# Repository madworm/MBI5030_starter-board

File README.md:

MBI5030_starter-board
=====================

LAYOUT FILES: Simple breadboard starter board for the MBI5030. Includes 16 SMD LEDs for instant light. 

You will find code for this project in [this](https://github.com/madworm/MBI5030_demo) repository.

---

Before having PC-boards made, please make sure you know about your manufacturer's peculiarities!
Especially drill-sizes and their tolerances may vary too much and give you trouble.

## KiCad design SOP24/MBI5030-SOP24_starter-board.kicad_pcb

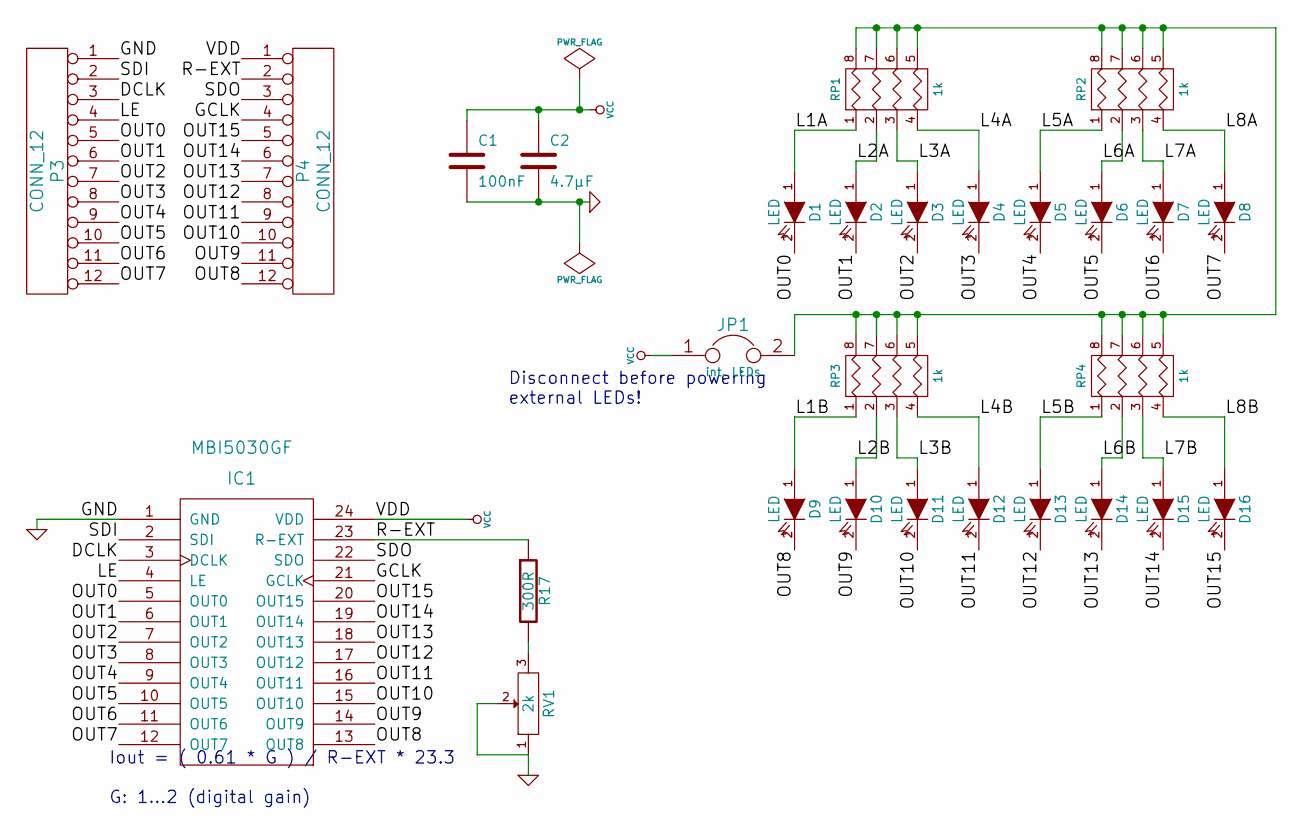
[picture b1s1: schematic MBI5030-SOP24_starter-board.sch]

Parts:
C1: 100nF
C2: 4.7µF
D1, D2, D3, D4, D5, D6, D7, D8, D9, D10, D11, D12, D13, D14, D15, D16: LED
IC1: MBI5030GF
JP1: int. LEDs
P3, P4: CONN_12
R17: 300R
RP1, RP2, RP3, RP4: 1k
RV1: 2k

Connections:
/DCLK: IC1.3 (DCLK), P3.3
/GCLK: IC1.21 (GCLK), P4.4
/L1A: D1.1 (A), RP1.1
/L1B: D9.1 (A), RP3.1
/L2A: D2.1 (A), RP1.2
/L2B: D10.1 (A), RP3.2
/L3A: D3.1 (A), RP1.3
/L3B: D11.1 (A), RP3.3
/L4A: D4.1 (A), RP1.4
/L4B: D12.1 (A), RP3.4
/L5A: D5.1 (A), RP2.1
/L5B: D13.1 (A), RP4.1
/L6A: D6.1 (A), RP2.2
/L6B: D14.1 (A), RP4.2
/L7A: D7.1 (A), RP2.3
/L7B: D15.1 (A), RP4.3
/L8A: D8.1 (A), RP2.4
/L8B: D16.1 (A), RP4.4
/LE: IC1.4 (LE), P3.4
/OUT0: D1.2 (K), IC1.5 (OUT0), P3.5
/OUT1: D2.2 (K), IC1.6 (OUT1), P3.6
/OUT2: D3.2 (K), IC1.7 (OUT2), P3.7
/OUT3: D4.2 (K), IC1.8 (OUT3), P3.8
/OUT4: D5.2 (K), IC1.9 (OUT4), P3.9
/OUT5: D6.2 (K), IC1.10 (OUT5), P3.10
/OUT6: D7.2 (K), IC1.11 (OUT6), P3.11
/OUT7: D8.2 (K), IC1.12 (OUT7), P3.12
/OUT8: D9.2 (K), IC1.13 (OUT8), P4.12
/OUT9: D10.2 (K), IC1.14 (OUT9), P4.11
/OUT10: D11.2 (K), IC1.15 (OUT10), P4.10
/OUT11: D12.2 (K), IC1.16 (OUT11), P4.9
/OUT12: D13.2 (K), IC1.17 (OUT12), P4.8
/OUT13: D14.2 (K), IC1.18 (OUT13), P4.7
/OUT14: D15.2 (K), IC1.19 (OUT14), P4.6
/OUT15: D16.2 (K), IC1.20 (OUT15), P4.5
/R-EXT: IC1.23 (R-EXT), P4.2, R17.1
/SDI: IC1.2 (SDI), P3.2
/SDO: IC1.22 (SDO), P4.3
GND: C1.2, C2.2, IC1.1 (GND), P3.1, RV1.1, RV1.2
unnamed: R17.2, RV1.3
unnamed: JP1.2, RP1.5 (R4), RP1.6 (R3), RP1.7 (R2), RP1.8 (R1), RP2.5 (R4), RP2.6 (R3), RP2.7 (R2), RP2.8 (R1), RP3.5 (R4), RP3.6 (R3), RP3.7 (R2), RP3.8 (R1), RP4.5 (R4), RP4.6 (R3), RP4.7 (R2), RP4.8 (R1)
VCC: C1.1, C2.1, IC1.24 (VDD), JP1.1, P4.1

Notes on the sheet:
Iout = ( 0.61 * G ) / R-EXT * 23.3 G: 1...2 (digital gain)
Disconnect before powering external LEDs!

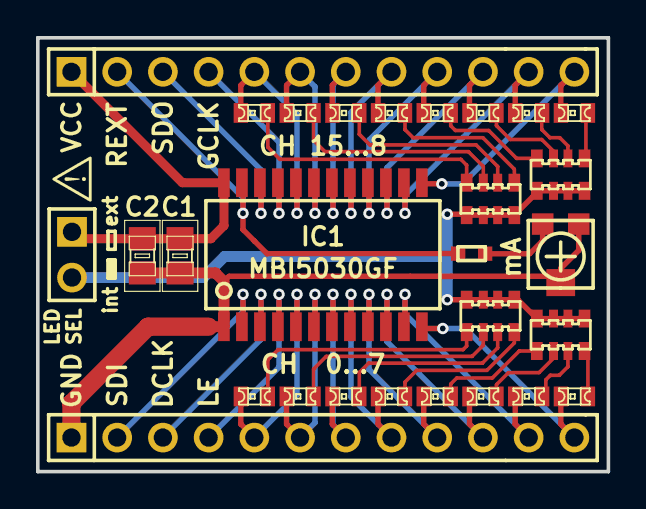
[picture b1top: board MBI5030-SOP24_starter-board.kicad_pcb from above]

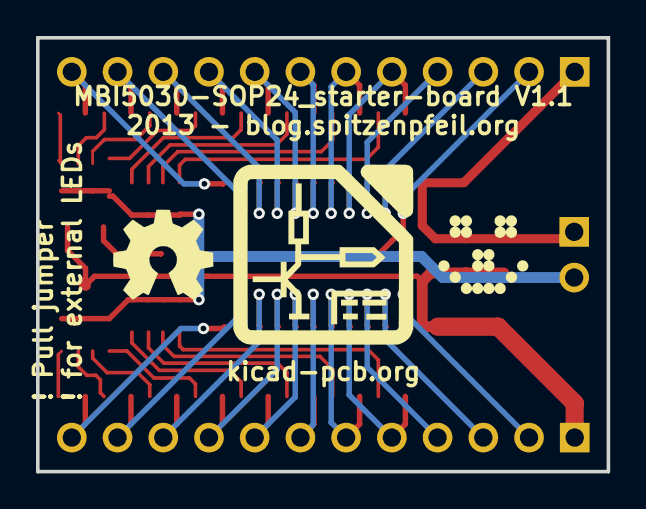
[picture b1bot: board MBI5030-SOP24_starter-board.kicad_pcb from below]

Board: 2 copper layers, 31.7 x 24.1 mm, 32 parts (3 on the bottom side), 42 nets.

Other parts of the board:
G1, G2, G3, G4: LOGO

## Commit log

2013-01-21 First doodles.
2013-01-21 Shifted a silly trace to where it belongs.
2013-01-21 Fixed old script.
2013-01-21 Moved README.md to a better spot.
2013-01-21 Board shrink. 1 more free row of pins on the breadboard.
2013-01-21 Added a board dimensions on a comment layer.
2013-01-21 Added a warning on B_SilkS to pull the jumper for external LEDs.
    This is especially important if their supply voltage is above VCC.
2013-01-21 Used smaller R0603 footprints and shifted them to better places.
2013-01-21 Silkscreen tweaks.
2013-01-22 Moved LED resistors. Tweezers are in fact not arbitrarily small.
2013-01-26 Much wider GND trace + minor tweaks to other traces.
2013-01-27 Behind the scenes stuff.
2013-01-29 Shifted LED-sel jumper + added a warning logo + info what to do.
2013-01-29 Added some text to F_SilkS.
2013-01-29 Working on a screw-terminal (plug-on) variant.
2013-01-29 Playing with the screw-terminal variant. Terminal blocks are HUGE ;-(
2013-02-01 Updated 'README.md'
2013-02-04 Tweaks. Only affects silkscreen. Didn't recreate gerbers.
2013-02-09 Increased pad-size of headers (annular ring) + 0603 LED footprint (wider pads).
2013-04-01 Created a panel.
2013-04-03 Replaced 0603 resistors with 1206 4x resistor packs.
2013-04-03 Upgraded the panel as well.
2013-04-05 Flipped one trace to F_Cu.
2013-04-22 Added formula to calculate a SAFE R-EXT.
2013-06-28 Converted to new kicad board format.
2013-07-08 Added gerber file for: F_Paste.
2014-07-18 Added simplified bill of materials file.
2014-07-18 Typo in BOM file.
2015-08-21 Added assembly tips.
2015-09-10 Added datasheet.
